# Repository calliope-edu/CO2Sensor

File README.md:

# Technical Documentation

[see here](https://calliope-edu.github.io/CO2Sensor)

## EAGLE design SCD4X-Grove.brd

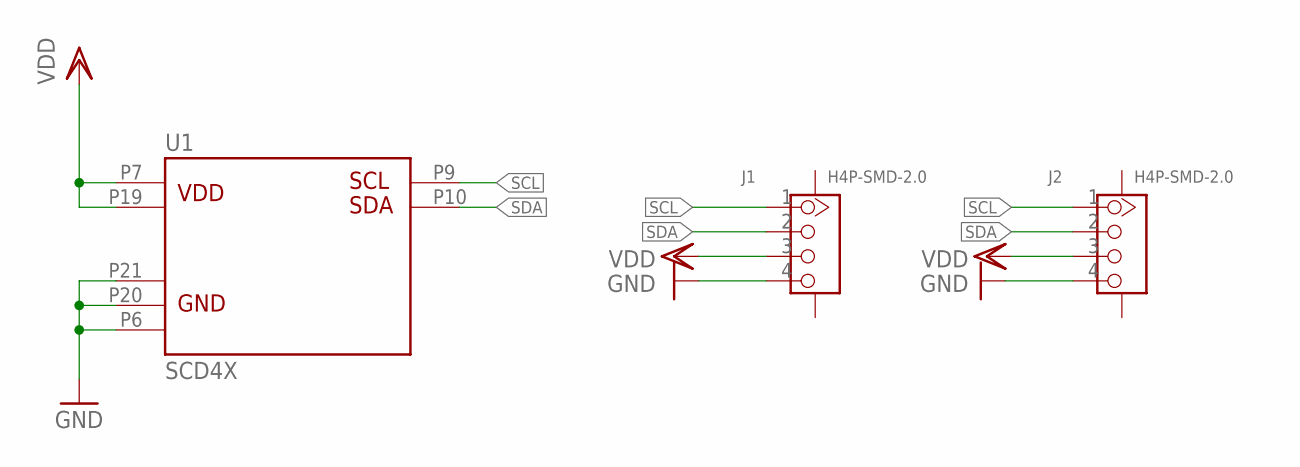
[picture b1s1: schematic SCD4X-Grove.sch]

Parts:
J1, J2: H4P-SMD-2.0; HW4-SMD-2.0
U1: SCD4X

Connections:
GND: J1.4, J2.4, U1.P6, U1.P20, U1.P21
SCL: J1.1, J2.1, U1.P9
SDA: J1.2, J2.2, U1.P10
VDD: J1.3, J2.3, U1.P7, U1.P19

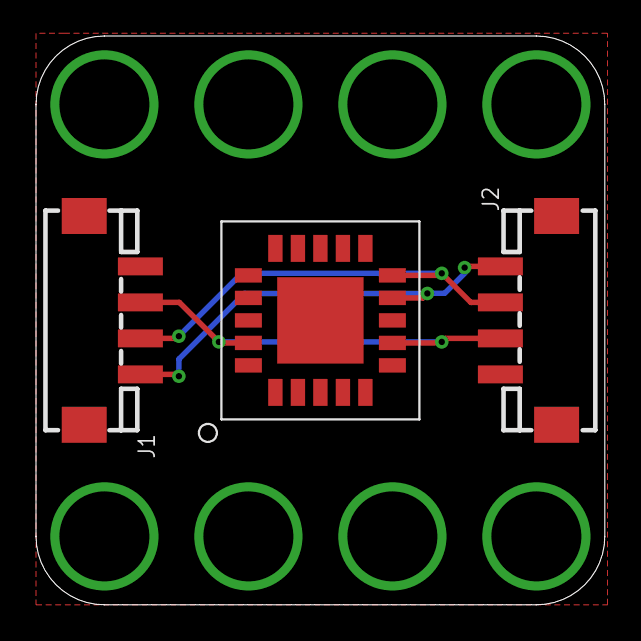
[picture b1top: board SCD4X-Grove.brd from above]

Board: 2 copper layers, 31.6 x 31.6 mm, 3 parts (0 on the bottom side), 4 nets.

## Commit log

2022-01-04 Set theme jekyll-theme-slate
2022-01-04 Updated structure
